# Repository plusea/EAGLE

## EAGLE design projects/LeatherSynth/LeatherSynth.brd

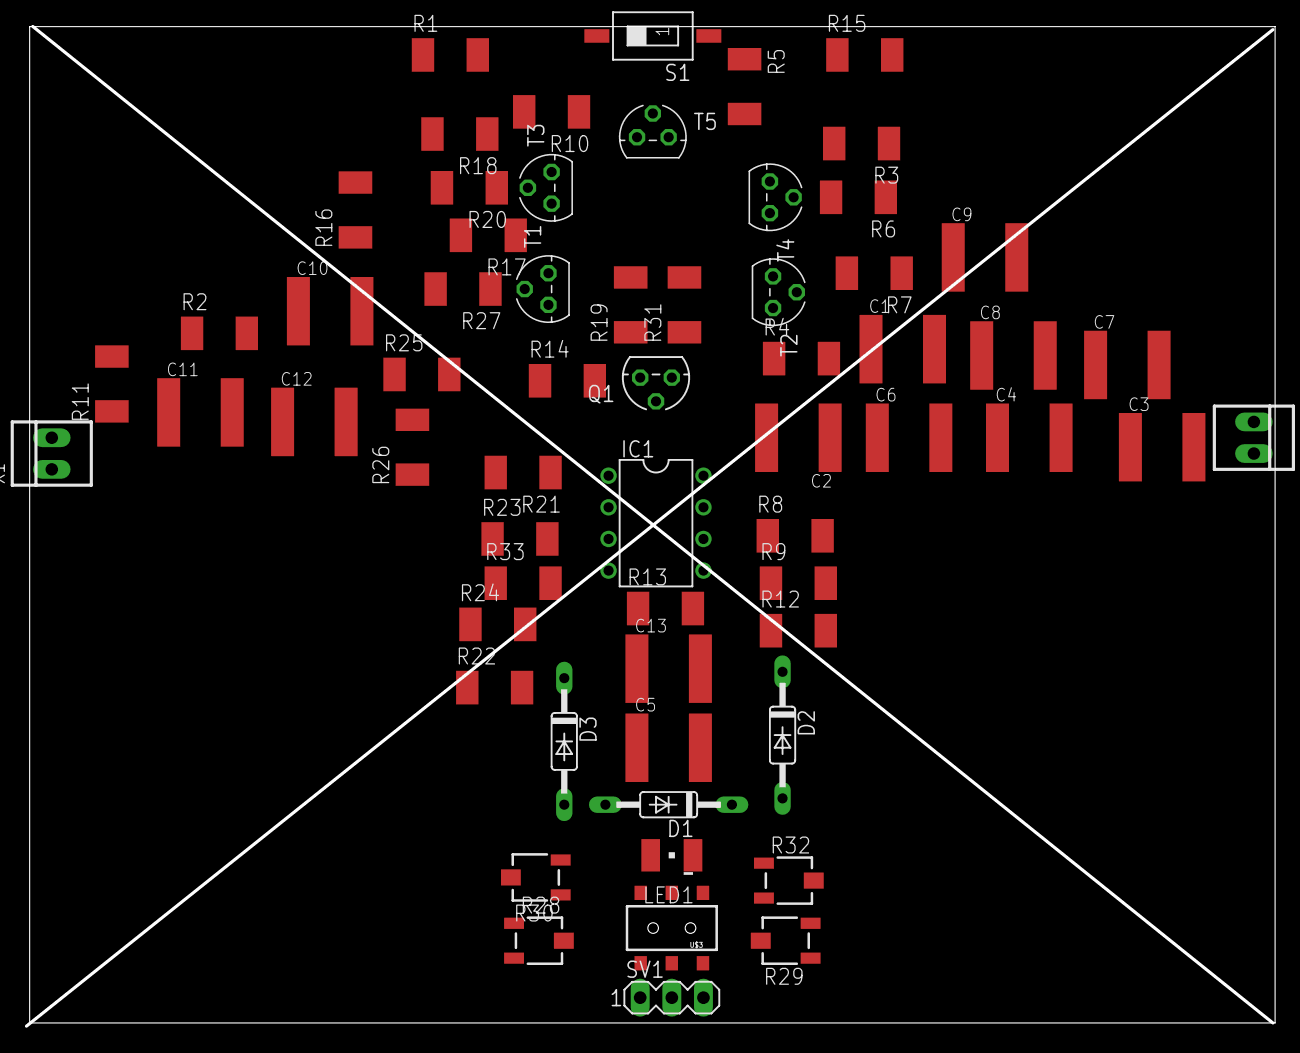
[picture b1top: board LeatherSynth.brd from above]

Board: 2 copper layers, 100.0 x 80.0 mm, 64 parts (0 on the bottom side), 36 nets, no tracks yet.

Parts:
C1, C5, C6, C7: 15nF; C2220K
C2: 220pF; C2220K
C3: 33nF; C2220K
C4, C8, C9: 100nF; C2220K
C10: 33uF; C2220K
C11: 1uF; C2220K
C12, C13: 0,47uF; C2220K
D1, D2, D3: 1N4148DO35-10; DO35-10
IC1: TL072P; DIL08
LED1: LG_T679-E1F1-1; PLCC2
Q1: BC557; TO92
R1: 220; R2010
R2: 1K; R2010
R3: 2,7K; R2010
R4, R14, R15: 4,7; R2010
R5: 6,8; R2010
R6: 8,2; R2010
R7, R16, R17, R18, R33: 10K; R2010
R8, R19, R20: 22K; R2010
R9, R21: 47K; R2010
R10: 82K; R2010
R11, R22, R23, R24, R25, R31: 100K; R2010
R12: 470K; R2010
R13, R26, R27: 1M; R2010
R28: 50K; 3223J
R29: 500K; 3223J
R30: 10K; 3223J
R32: 100K; 3223J
S1: SWS001; SMS-001
SV1: MA03-1
T1, T2, T3, T4, T5: BC547; TO92
U$1: LEATHERSYNTH
U$2: LEATHERSYNTH2
U$3: AYZ0202
X1, X2: 22-23-2021

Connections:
+9V: IC1.8, LED1.A, R19.2, R27.2, R31.2, S1.2, SV1.3
-9V: IC1.4, R5.1, R33.1, SV1.1
GND: C2.2, C4.2, C8.2, D1.C, D2.A, R3.1, R4.1, R8.1, R11.1, R18.1, R24.1, R25.1, R28.2, R32.1, T1.1, T2.1, T3.1, T4.1, U$3.2, X1.2, X2.2
unnamed: R12.1, R13.2
unnamed: C3.2, IC1.7, R9.2, R12.2
unnamed: C10.1, R19.1, R23.1, T1.3
unnamed: IC1.5, R9.1, R21.2, R29.1
unnamed: IC1.6, R8.2
unnamed: C3.1, R29.2
unnamed: C5.2, IC1.1, R21.1, R26.2
unnamed: R16.2, R30.3
unnamed: C4.1, C12.1, R16.1, R30.1, R30.2
unnamed: C12.2, R32.3
unnamed: C13.1, R32.2
unnamed: C13.2, R10.1
unnamed: R10.2, R25.2, T5.2
unnamed: C11.1, R2.1, R11.2
unnamed: LED1.C, R33.2
unnamed: C2.1, C11.2, R5.2, T5.1
unnamed: SV1.2, U$3.1
unnamed: C10.2, D1.A, R13.1
unnamed: C1.2, C5.1, R7.1
unnamed: R7.2, R28.3, T2.3
unnamed: C1.1, IC1.3, R23.2, R26.1, T2.2
unnamed: C6.2, D2.C, IC1.2, R4.2, R22.2
unnamed: C8.1, R27.1, T1.2, T4.3
unnamed: R3.2, R6.2, T4.2
unnamed: C6.1, Q1.3, R6.1, R22.1
unnamed: Q1.1, R14.2, R31.1
unnamed: Q1.2, R14.1, R17.2
unnamed: R17.1, T3.3
unnamed: D3.A, S1.1
unnamed: C9.1, D3.C, R24.2
unnamed: C9.2, R20.2
unnamed: R18.2, R20.1, T3.2
unnamed: R2.2, X1.1, X2.1

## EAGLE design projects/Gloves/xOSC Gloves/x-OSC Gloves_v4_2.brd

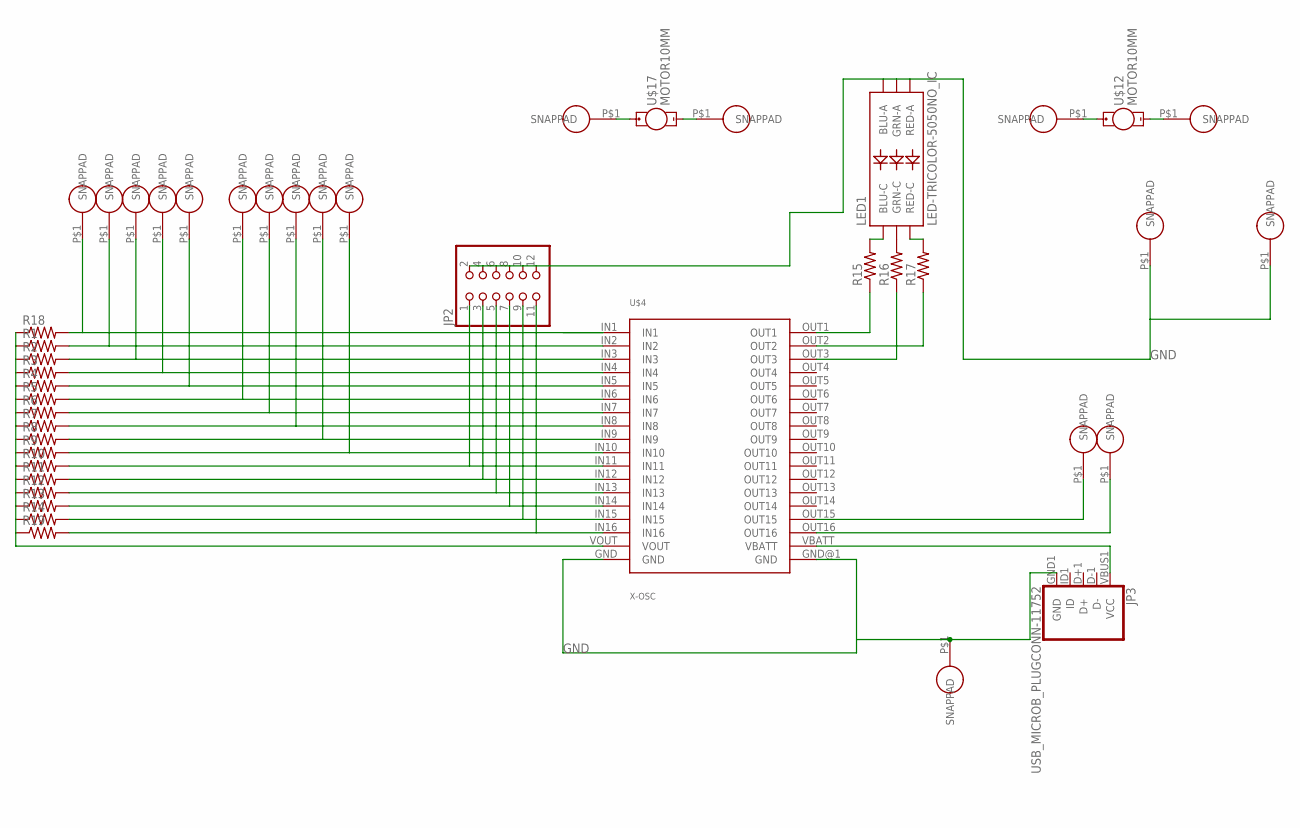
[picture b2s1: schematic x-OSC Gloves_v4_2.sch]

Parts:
JP2: PINHD-2X6/90; 2X06/90
JP3: USB_MICROB_PLUGCONN-11752; USB-B-MICRO-SMD_V03
LED1: LED-TRICOLOR-5050NO_IC; LED-TRICOLOR-5050
R1, R2, R3, R4, R5, R6, R7, R8, R9, R10, R11, R12, R13, R14, R15, R16, R17, R18, R19: RESISTOR0805-RES; 0805
U$1, U$2, U$3, U$6, U$7, U$8, U$9, U$10, U$11, U$13, U$14, U$15, U$16, U$18, U$19, U$20, U$21, U$22, U$23: SNAP-PAD_7MM_ROUND; SNAP-PAD_7MM_RD
U$4: X-OSC; X-OSC_SMD
U$12, U$17: MOTOR10MM; VIBE-MOTOR-10MM

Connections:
GND: JP2.2, JP2.4, JP2.6, JP2.8, JP2.10, JP2.12, JP3.GND1 (GND), LED1.1 (GRN-A), LED1.2 (RED-A), LED1.3 (BLU-A), U$4.GND, U$4.GND@1 (GND), U$15.P$1, U$16.P$1, U$18.P$1
unnamed: LED1.6 (GRN-C), R16.2
unnamed: LED1.4 (BLU-C), R15.2
unnamed: R16.1, U$4.OUT3
unnamed: R1.2, U$1.P$1, U$4.IN2
unnamed: R2.2, U$2.P$1, U$4.IN3
unnamed: R3.2, U$3.P$1, U$4.IN4
unnamed: R4.2, U$4.IN5, U$6.P$1
unnamed: R5.2, U$4.IN6, U$7.P$1
unnamed: R6.2, U$4.IN7, U$8.P$1
unnamed: R7.2, U$4.IN8, U$9.P$1
unnamed: R8.2, U$4.IN9, U$10.P$1
unnamed: R9.2, U$4.IN10, U$11.P$1
unnamed: JP2.1, R10.2, U$4.IN11
unnamed: LED1.5 (RED-C), R17.2
unnamed: JP2.3, R11.2, U$4.IN12
unnamed: JP2.5, R12.2, U$4.IN13
unnamed: JP2.7, R13.2, U$4.IN14
unnamed: JP2.9, R14.2, U$4.IN15
unnamed: JP2.11, R19.2, U$4.IN16
unnamed: U$4.OUT15, U$13.P$1
unnamed: U$4.OUT16, U$14.P$1
unnamed: R17.1, U$4.OUT2
unnamed: R15.1, U$4.OUT1
unnamed: U$12.+, U$22.P$1
unnamed: U$12.-, U$23.P$1
unnamed: JP3.VBUS1 (VCC), U$4.VBATT
unnamed: U$17.+, U$19.P$1
unnamed: R18.2, U$4.IN1, U$21.P$1
unnamed: U$17.-, U$20.P$1
unnamed: R1.1, R2.1, R3.1, R4.1, R5.1, R6.1, R7.1, R8.1, R9.1, R10.1, R11.1, R12.1, R13.1, R14.1, R18.1, R19.1, U$4.VOUT

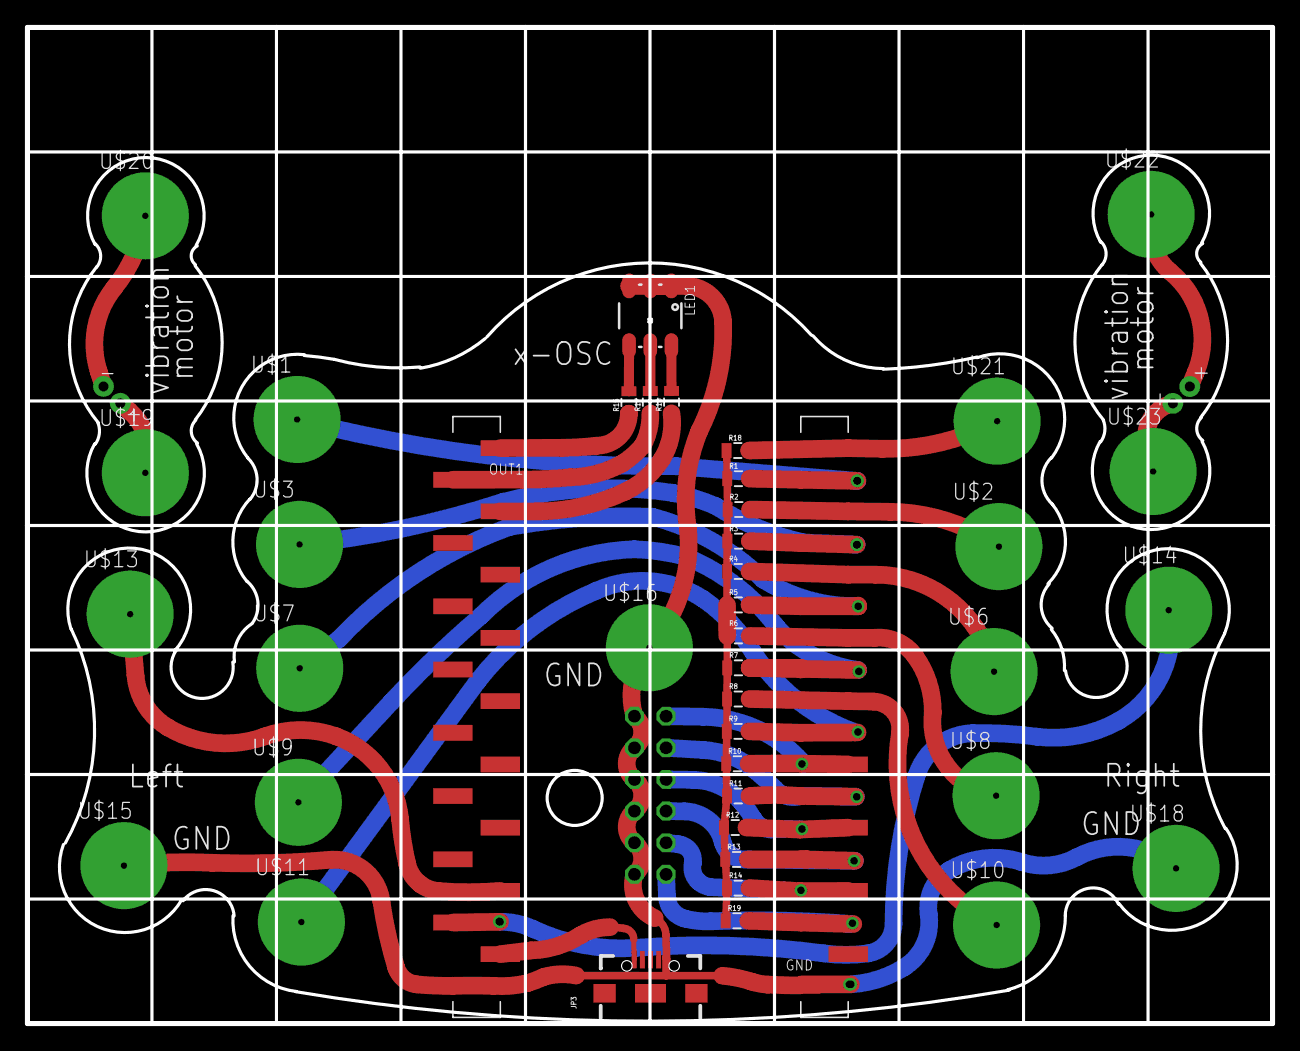
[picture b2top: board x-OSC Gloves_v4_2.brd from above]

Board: 2 copper layers, 100.0 x 80.0 mm, 44 parts (1 on the bottom side), 31 nets.

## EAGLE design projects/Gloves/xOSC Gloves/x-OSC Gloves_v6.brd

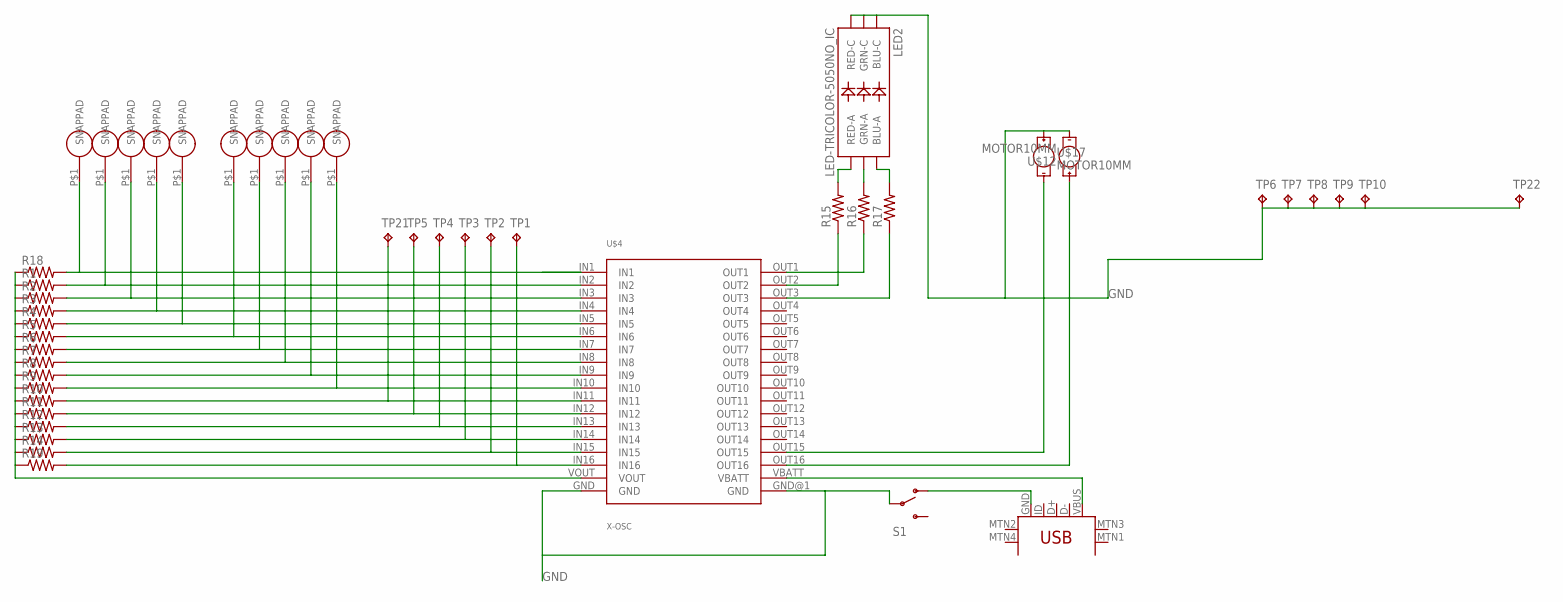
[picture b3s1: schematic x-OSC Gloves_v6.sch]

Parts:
LED2: LED-TRICOLOR-5050NO_IC; LED-TRICOLOR-5050
R1, R2, R3, R4, R5, R6, R7, R8, R9, R10, R11, R12, R13, R14, R15, R16, R17, R18, R19: RESISTOR0805-RES; 0805
S1: SWITCH-SPDT-SMD-A; SWITCH-SPST-SMD-A
TP1, TP2, TP3, TP4, TP5, TP6, TP7, TP8, TP9, TP10, TP21, TP22: TPTP20R; TP20R
U$1, U$2, U$3, U$6, U$7, U$8, U$9, U$10, U$11, U$21: SNAP-PAD_7MM_ROUND; SNAP-PAD_7MM_RD
U$4: X-OSC; X-OSC_SMD
U$5: USB-MINIB-5PIN; USB-MINIB
U$12, U$17: MOTOR10MM; VIBE-MOTOR-10MM

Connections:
GND: LED2.4 (BLU-C), LED2.5 (RED-C), LED2.6 (GRN-C), S1.2, TP6.TP, TP7.TP, TP8.TP, TP9.TP, TP10.TP, TP22.TP, U$4.GND, U$4.GND@1 (GND), U$12.-, U$17.+
unnamed: LED2.1 (GRN-A), R16.2
unnamed: LED2.2 (RED-A), R15.2
unnamed: R15.1, U$4.OUT2
unnamed: R1.2, U$1.P$1, U$4.IN2
unnamed: R16.1, U$4.OUT1
unnamed: R2.2, U$2.P$1, U$4.IN3
unnamed: R3.2, U$3.P$1, U$4.IN4
unnamed: R4.2, U$4.IN5, U$6.P$1
unnamed: R5.2, U$4.IN6, U$7.P$1
unnamed: R6.2, U$4.IN7, U$8.P$1
unnamed: R7.2, U$4.IN8, U$9.P$1
unnamed: R8.2, U$4.IN9, U$10.P$1
unnamed: R9.2, U$4.IN10, U$11.P$1
unnamed: R10.2, TP21.TP, U$4.IN11
unnamed: LED2.3 (BLU-A), R17.2
unnamed: R11.2, TP5.TP, U$4.IN12
unnamed: R12.2, TP4.TP, U$4.IN13
unnamed: R13.2, TP3.TP, U$4.IN14
unnamed: R14.2, TP2.TP, U$4.IN15
unnamed: R19.2, TP1.TP, U$4.IN16
unnamed: U$4.OUT15, U$17.-
unnamed: U$4.OUT16, U$12.+
unnamed: R17.1, U$4.OUT3
unnamed: S1.1 (O), U$5.GND
unnamed: U$4.VBATT, U$5.VBUS
unnamed: R18.2, U$4.IN1, U$21.P$1
VDD: R1.1, R2.1, R3.1, R4.1, R5.1, R6.1, R7.1, R8.1, R9.1, R10.1, R11.1, R12.1, R13.1, R14.1, R18.1, R19.1, U$4.VOUT

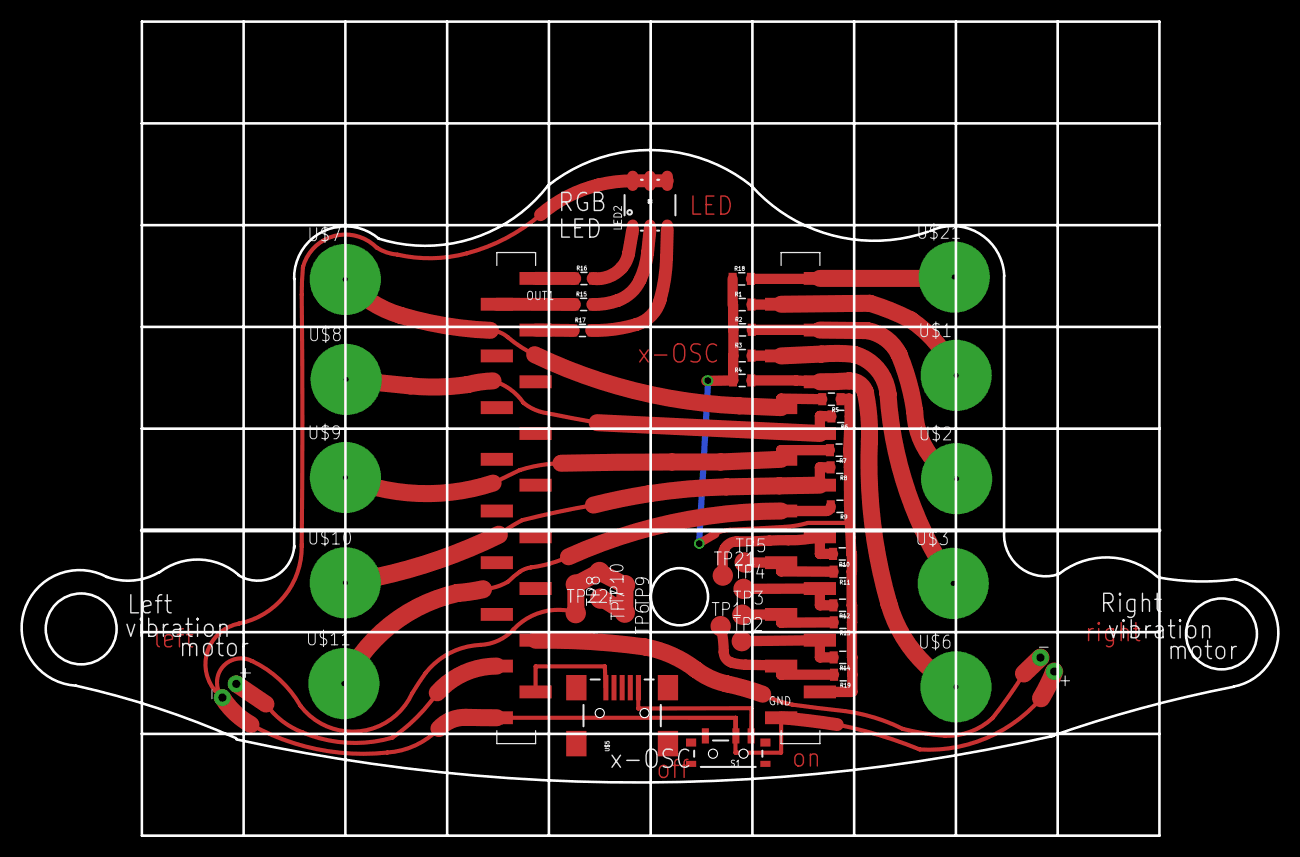
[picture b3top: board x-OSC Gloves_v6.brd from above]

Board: 2 copper layers, 100.0 x 80.0 mm, 47 parts (0 on the bottom side), 28 nets.

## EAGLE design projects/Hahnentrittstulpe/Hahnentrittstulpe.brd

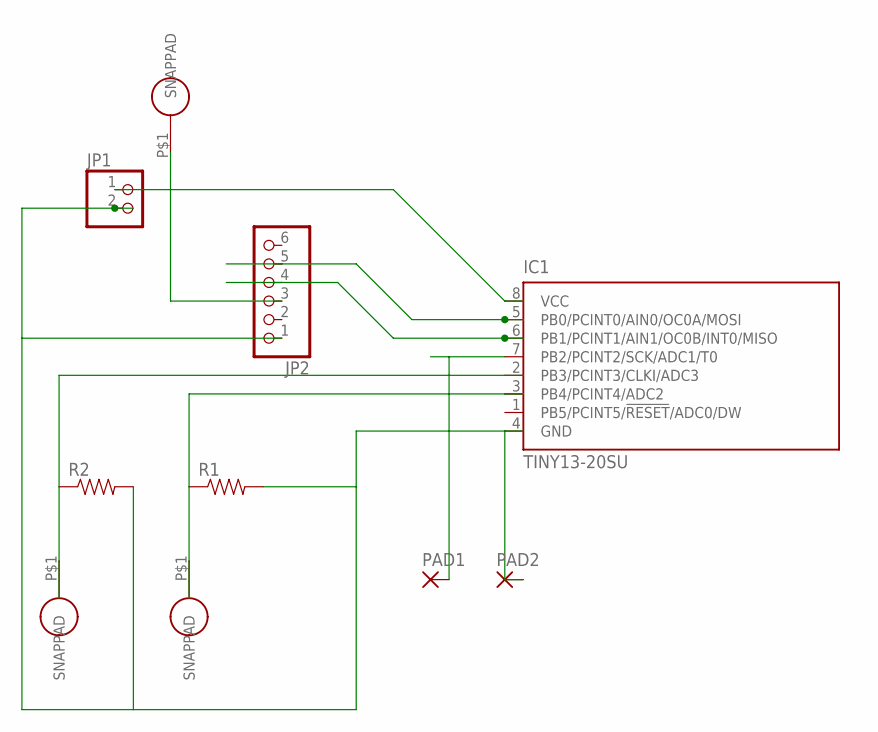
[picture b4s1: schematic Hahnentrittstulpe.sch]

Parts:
IC1: TINY13-20SU; 8S2
JP1: PINHD-1X2; 1X02
JP2: PINHD-1X6/90; 1X06/90
PAD1, PAD2: SMD2; SMD1,27-2,54
R1, R2: RESISTOR0805-RES; 0805
U$1, U$2, U$3: SNAP-PAD_7MM_ROUND; SNAP-PAD_7MM_RD

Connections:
unnamed: IC1.3 (PB4/PCINT4/ADC2), R1.1, U$1.P$1
unnamed: IC1.2 (PB3/PCINT3/CLKI/ADC3), R2.1, U$2.P$1
unnamed: IC1.7 (PB2/PCINT2/SCK/ADC1/T0), PAD1.1
unnamed: IC1.8 (VCC), JP1.1, JP2.3, U$3.P$1
unnamed: IC1.6 (PB1/PCINT1/AIN1/OC0B/INT0/MISO), JP2.4
unnamed: IC1.5 (PB0/PCINT0/AIN0/OC0A/MOSI), JP2.5
unnamed: IC1.4 (GND), JP1.2, JP2.1, PAD2.1, R1.2, R2.2

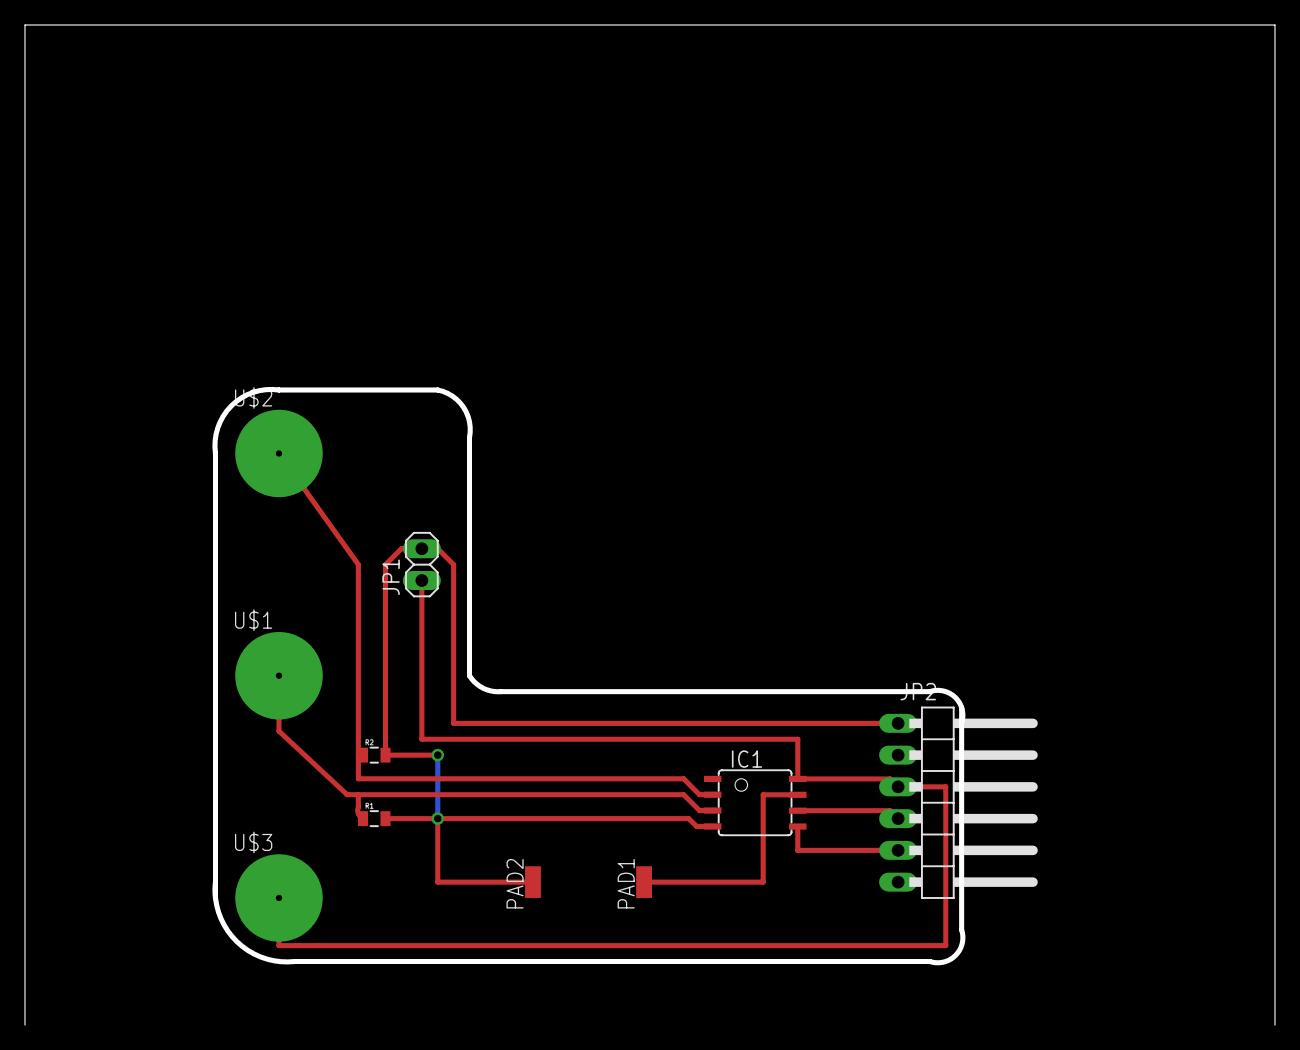
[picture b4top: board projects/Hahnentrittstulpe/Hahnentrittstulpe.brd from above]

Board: 2 copper layers, 59.8 x 45.9 mm, 10 parts (0 on the bottom side), 7 nets.

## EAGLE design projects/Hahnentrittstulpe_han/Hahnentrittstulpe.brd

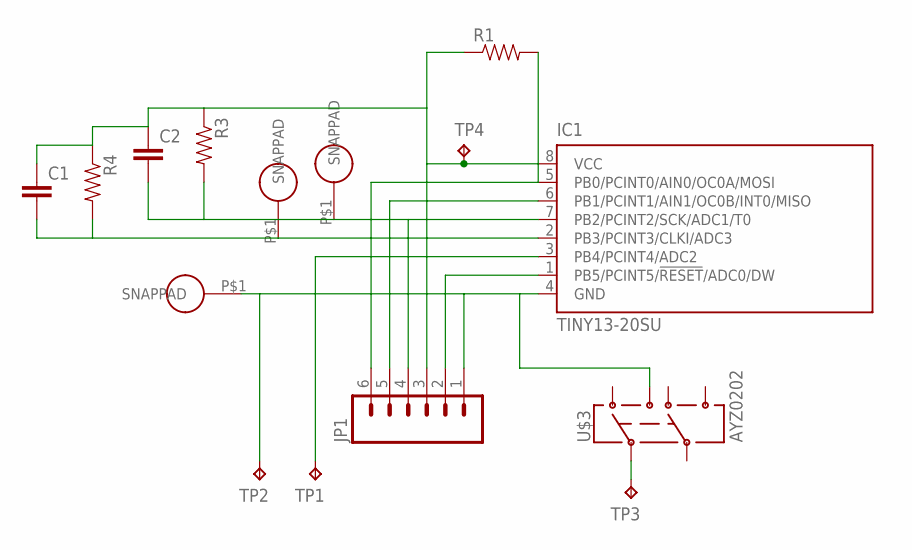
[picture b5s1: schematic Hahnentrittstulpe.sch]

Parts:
C1, C2: CAP0603-CAP; 0603-CAP
IC1: TINY13-20SU; 8S2
JP1: M06SMD; 1X06-SMD
R1: RESISTOR1206; 1206
R3, R4: RESISTOR0402-RES; 0402-RES
TP1, TP2, TP3, TP4: TPTP18SQ; TP18SQ
U$1, U$2, U$4: SNAP-PAD_7MM_ROUND; SNAP-PAD_7MM_RD
U$3: AYZ0202

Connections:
unnamed: IC1.1 (PB5/PCINT5/!RESET!/ADC0/DW), JP1.2
unnamed: IC1.3 (PB4/PCINT4/ADC2), TP1.TP
unnamed: C1.2, IC1.2 (PB3/PCINT3/CLKI/ADC3), R4.2, U$1.P$1
unnamed: C2.2, IC1.7 (PB2/PCINT2/SCK/ADC1/T0), JP1.4, R3.2, U$2.P$1
unnamed: IC1.4 (GND), JP1.1, TP2.TP, U$3.1 (3), U$4.P$1
unnamed: C1.1, C2.1, IC1.8 (VCC), JP1.3, R1.1, R3.1, R4.1, TP4.TP
unnamed: IC1.6 (PB1/PCINT1/AIN1/OC0B/INT0/MISO), JP1.5
unnamed: IC1.5 (PB0/PCINT0/AIN0/OC0A/MOSI), JP1.6, R1.2
unnamed: TP3.TP, U$3.2

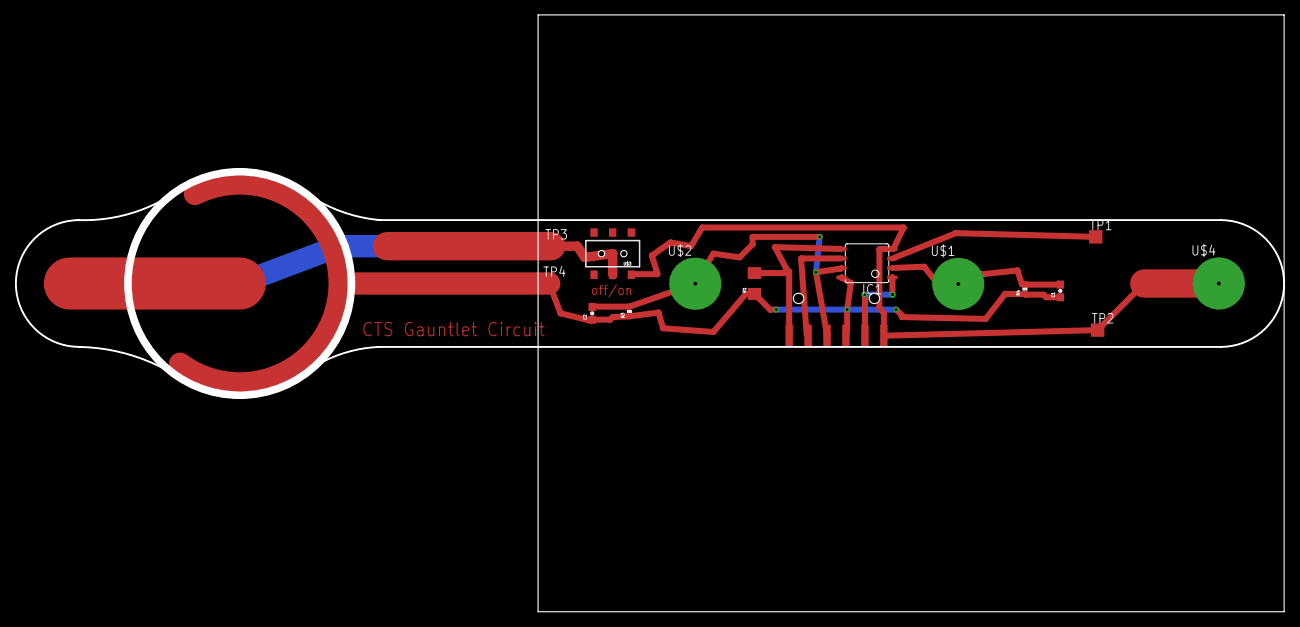
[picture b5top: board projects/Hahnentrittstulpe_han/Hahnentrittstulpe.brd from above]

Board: 2 copper layers, 170.0 x 80.0 mm, 15 parts (0 on the bottom side), 9 nets.

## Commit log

2013-05-16 eagle
2013-05-16 for etching
2013-06-27 attiny board
2013-06-29 flex pcb stuff
2013-07-24 adding laptop files
2013-07-25 good version of ATtinyBoard!
2013-07-25 folder re-ordering
2013-08-05 xOSC circuit
2013-08-05 xOSC update
2013-08-06 xosc gloves
2013-08-07 eagle folder structure redo
2013-08-07 eagle lib del
2013-08-13 adding udk files
2013-08-15 push to merge
2013-09-02 MegaGlove final baord
2013-09-12 traces with origin
2013-09-13 traces with origin final
2013-11-08 glove
2013-12-02 x-OSC flex with usb mini power
2013-12-13 gloves updates
2014-08-17 final stulpe
2014-08-27 808 drum
2016-05-03 Update copy-wire-to-solder-mask.ulp
    Fixes problem with Wire Circle Arc not being copied to the solder mask layer.

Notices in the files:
parts and their libraries:
SparkFun-Passives: Licensing: CC v3.0 Share-Alike You are welcome to use this library for commercial purposes.
